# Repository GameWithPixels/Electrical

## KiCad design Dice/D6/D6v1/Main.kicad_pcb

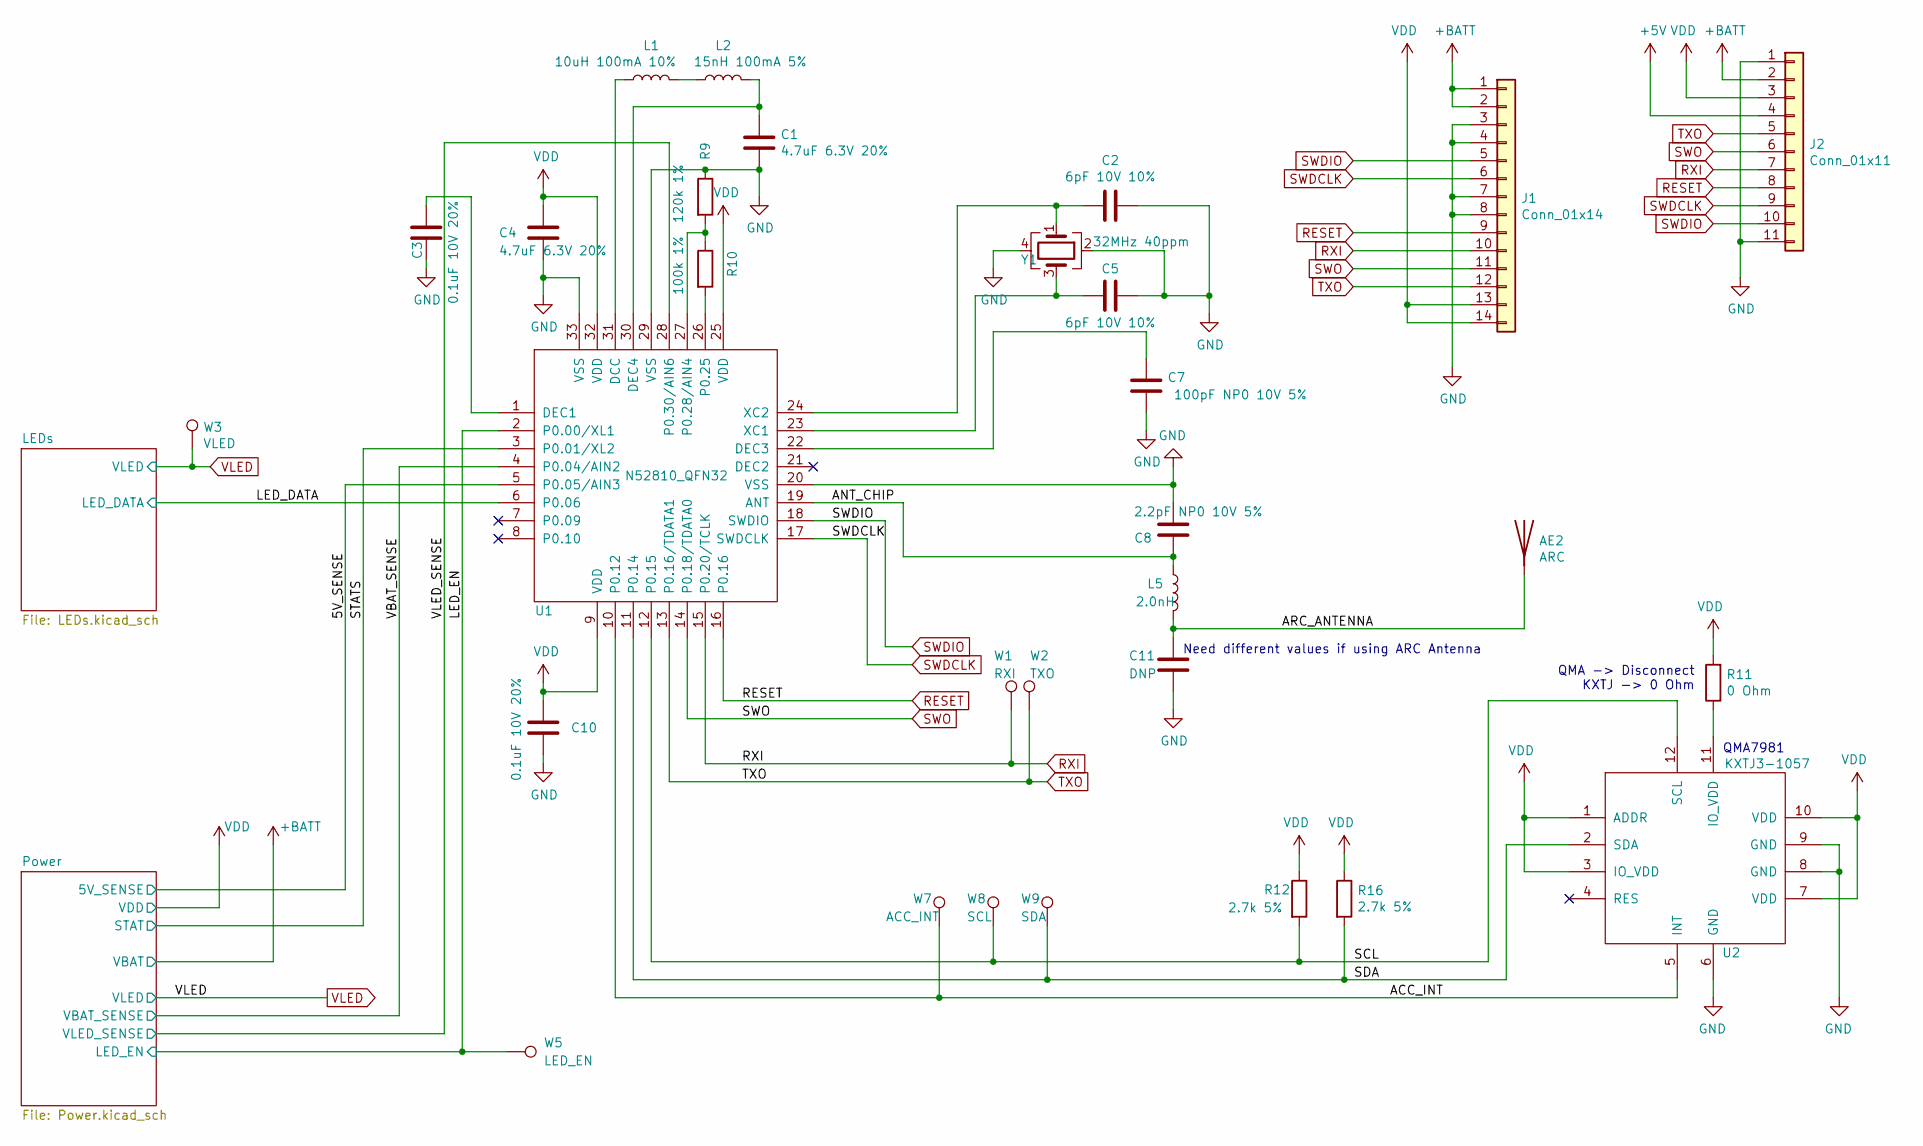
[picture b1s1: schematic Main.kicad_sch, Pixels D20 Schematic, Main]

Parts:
AE2: ARC; ARC_Antenna
C1, C4: 4.7uF 6.3V 20%; C_0402_1005Metric; Manufacturer Part Number GRM155R60J475ME87D
C2, C5: 6pF 10V 10%; C_0402_1005Metric; Manufacturer Part Number GCM1555C1H6R0DA16D
C3, C10: 0.1uF 10V 20%; C_0402_1005Metric; Manufacturer Part Number GRM155R61H104KE19D
C7: 100pF NP0 10V 5%; C_0402_1005Metric; Manufacturer Part Number C0402C101J5GAC7411
C8: 2.2pF NP0 10V 5%; C_0402_1005Metric
C11: DNP; C_0402_1005Metric
J1: Conn_01x14; FPC_14
J2: Conn_01x11; FPC-POGO-11
L1: 10uH 100mA 10%; L_0805_2012Metric; Manufacturer Part Number LBR2012T100K
L2: 15nH 100mA 5%; L_0402_1005Metric; Manufacturer Part Number HK100515NJ-T
L5: 2.0nH; L_0402_1005Metric
R9: 120k 1%; R_0402_1005Metric; Manufacturer Part Number CRCW0402100KFKEDC
R10: 100k 1%; R_0402_1005Metric; Manufacturer Part Number CRCW0402100KFKEDC
R11: 0 Ohm; R_0402_1005Metric; Manufacturer Part Number AC0402FR-070RL
R12, R16: 2.7k 5%; R_0402_1005Metric; Manufacturer Part Number RC0402JR-072K7L
U1: N52810_QFN32; QFN-32-1EP_5x5mm_P0.5mm_EP3.1x3.1mm; Manufacturer Part Number NRF52810-QCAA-R
U2: KXTJ3-1057; LGA-12_2x2mm_P0.5mm; Manufacturer Part Number KXTJ3-1057
W1: RXI; TEST_PIN
W2: TXO; TEST_PIN
W3: VLED; TEST_PIN
W5: LED_EN; TEST_PIN
W7: ACC_INT; TEST_PIN
W8: SCL; TEST_PIN
W9: SDA; TEST_PIN
Y1: 32MHz 40ppm; Crystal_SMD_2016-4Pin_2.0x1.6mm; Manufacturer Part Number XRCGB32M000F2P00R0

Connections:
+5V: J2.4; also elsewhere on the board
+BATT: J1.1, J1.2, J2.2; also elsewhere on the board
/5V_SENSE: U1.5 (P0.05/AIN3); also elsewhere on the board
/ACC_INT: U1.10 (P0.12), U2.5 (INT), W7.1
/ANT_CHIP: C8.1, L5.1, U1.19 (ANT)
/ARC_ANTENNA: AE2.1 (A), C11.1, L5.2
/LED_DATA: U1.6 (P0.06); also elsewhere on the board
/LED_EN: U1.2 (P0.00/XL1), W5.1; also elsewhere on the board
/SCL: R12.2, U1.12 (P0.15), U2.12 (SCL), W8.1
/SDA: R16.2, U1.11 (P0.14), U2.2 (SDA), W9.1
/STATS: U1.3 (P0.01/XL2); also elsewhere on the board
/VBAT_SENSE: U1.4 (P0.04/AIN2); also elsewhere on the board
/VLED_SENSE: U1.28 (P0.30/AIN6); also elsewhere on the board
GND: C1.2, C2.1, C3.2, C4.2, C5.1, C7.2, C8.2, C10.2, C11.2, J1.3, J1.4, J1.7, J1.8, J2.1, J2.11, R9.1, U1.20 (VSS), U1.29 (VSS), U1.33 (VSS), U2.6 (GND), U2.8 (GND), U2.9 (GND), Y1.2, Y1.4; also elsewhere on the board
unnamed: C1.1, L2.2, U1.30 (DEC4)
unnamed: C2.2, U1.24 (XC2), Y1.1
unnamed: C3.1, U1.1 (DEC1)
unnamed: C5.2, U1.23 (XC1), Y1.3
unnamed: C7.1, U1.22 (DEC3)
unnamed: L1.1, U1.31 (DCC)
unnamed: L1.2, L2.1
unnamed: R9.2, R10.1, U1.27 (P0.28/AIN4)
unnamed: R10.2, U1.26 (P0.25)
unnamed: R11.1, U2.11 (IO_VDD)
RESET: J1.9, J2.8, U1.16 (P0.16)
RXI: J1.10, J2.7, U1.15 (P0.20/TCLK), W1.1
SWDCLK: J1.6, J2.9, U1.17 (SWDCLK)
SWDIO: J1.5, J2.10, U1.18 (SWDIO)
SWO: J1.11, J2.6, U1.14 (P0.18/TDATA0)
TXO: J1.12, J2.5, U1.13 (P0.16/TDATA1), W2.1
VDD: C4.1, C10.1, J1.13, J1.14, J2.3, R11.2, R12.1, R16.1, U1.9 (VDD), U1.25 (VDD), U1.32 (VDD), U2.1 (ADDR), U2.3 (IO_VDD), U2.7 (VDD), U2.10 (VDD); also elsewhere on the board
VLED: W3.1; also elsewhere on the board

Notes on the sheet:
QMA -> Disconnect KXTJ -> 0 Ohm
Need different values if using ARC Antenna
QMA7981

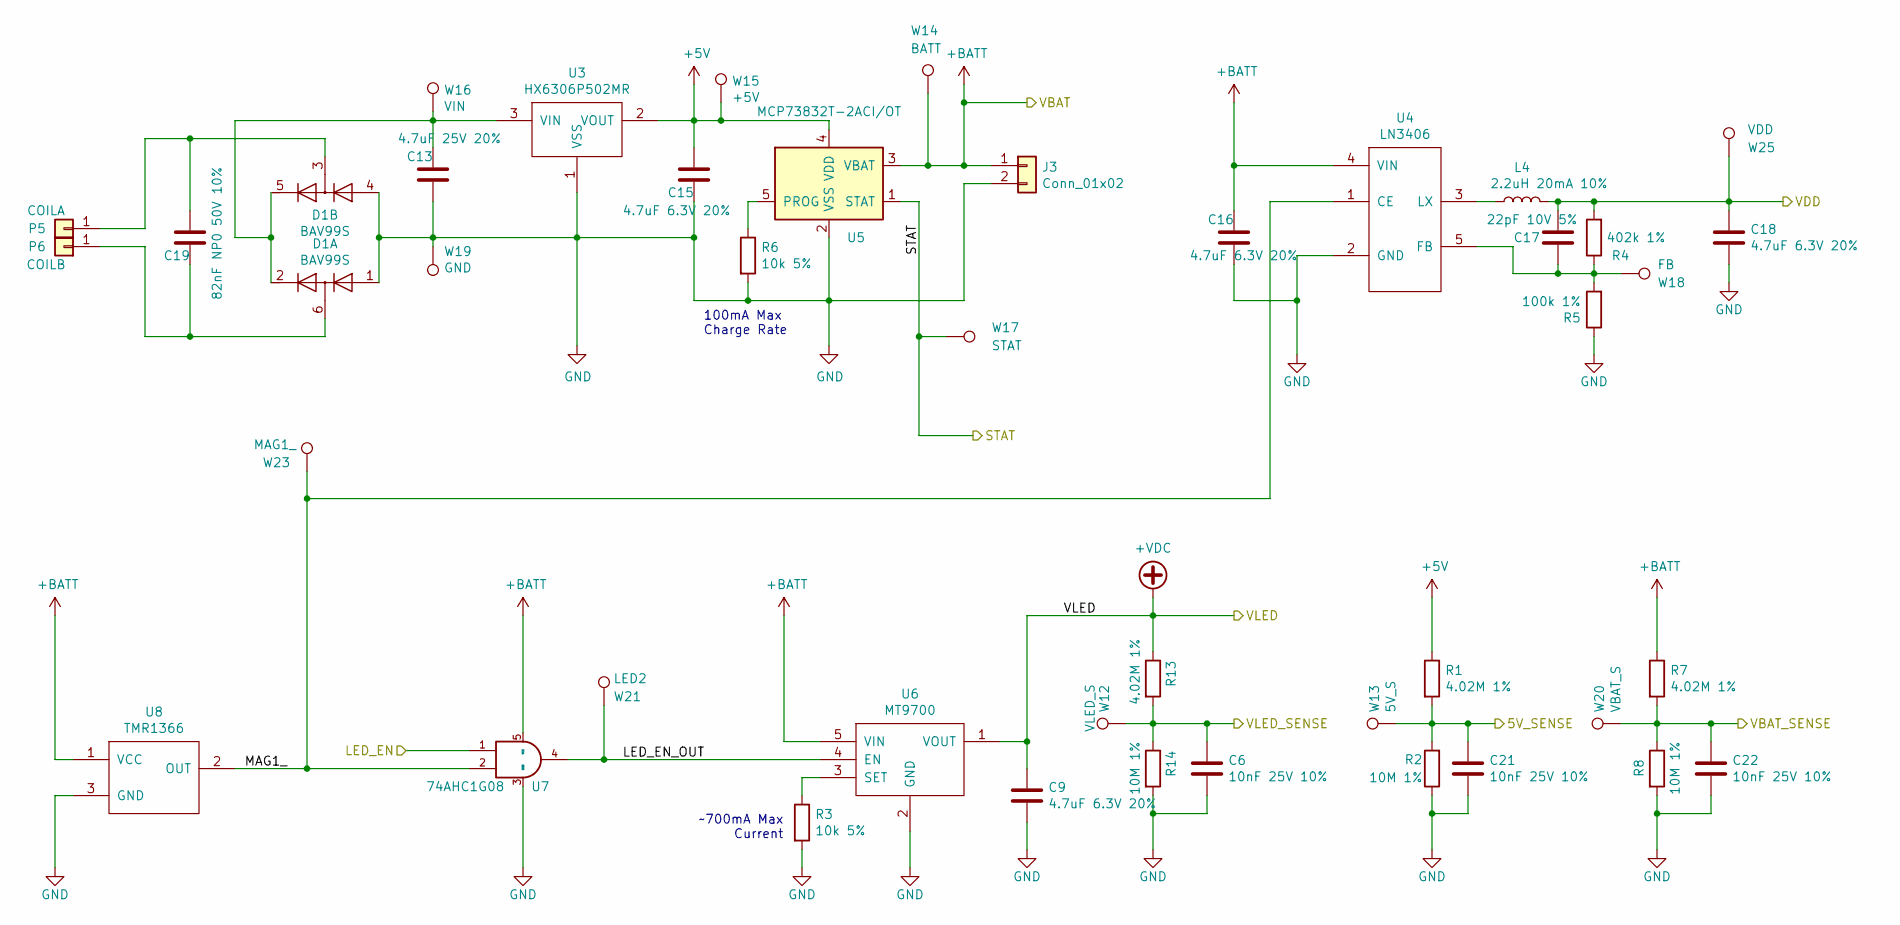
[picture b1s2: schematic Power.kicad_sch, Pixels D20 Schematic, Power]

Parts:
C6, C21, C22: 10nF 25V 10%; C_0402_1005Metric; Manufacturer Part Number AC0402KPX7R9BB103
C9, C15, C16, C18: 4.7uF 6.3V 20%; C_0402_1005Metric; Manufacturer Part Number GRM155R60J475ME87D
C13: 4.7uF 25V 20%; C_0603_1608Metric; Manufacturer Part Number GRM188R61E475KE11D
C17: 22pF 10V 5%; C_0402_1005Metric; Manufacturer Part Number CC0402JRNPO9BN220
C19: 82nF NP0 50V 10%; C_0805_2012Metric
D1: BAV99S; SOT-363_SC-70-6; Manufacturer Part Number BAV99SH6327XTSA1
J3: Conn_01x02; Hongjie 10100 Connector
L4: 2.2uH 20mA 10%; L_0805_2012Metric; Manufacturer Part Number CV201210-2R2K
P5: COILA; TestPoint_THTPad_D1.5mm_Drill0.7mm
P6: COILB; TestPoint_THTPad_D1.5mm_Drill0.7mm
R1, R7, R13: 4.02M 1%; R_0402_1005Metric; Manufacturer Part Number CRCW04024M02FKED
R2, R8, R14: 10M 1%; R_0402_1005Metric; Manufacturer Part Number RC0402FR-0710ML
R3, R6: 10k 5%; R_0402_1005Metric; Manufacturer Part Number RC0402JR-0710KL
R4: 402k 1%; R_0402_1005Metric; Manufacturer Part Number RC0402FR-07402KL
R5: 100k 1%; R_0402_1005Metric; Manufacturer Part Number CRCW0402100KFKEDC
U3: HX6306P502MR; SOT-23; Manufacturer Part Number HX6306P502MR
U4: LN3406; SOT-23-5; Manufacturer Part Number XT3406AFMR-G
U5: MCP73832T-2ACI/OT; SOT-23-5; Manufacturer Part Number MCP73832T-2ACI/OT
U6: MT9700; SOT-23-5; Manufacturer Part Number MT9700
U7: 74AHC1G08; SOT-353_SC-70-5; Manufacturer Part Number SN74AHC1G08DCKR
U8: TMR1366; SOT-23; Manufacturer Part Number TMR1366S
W12: VLED_S; TEST_PIN
W13: 5V_S; TEST_PIN
W14: BATT; TEST_PIN
W15: +5V; TEST_PIN
W16: VIN; TEST_PIN
W17: STAT; TEST_PIN
W18: FB; TEST_PIN
W19: GND; TEST_PIN
W20: VBAT_S; TEST_PIN
W21: LED2; TEST_PIN
W23: MAG1_; TEST_PIN
W25: VDD; TEST_PIN

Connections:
+5V: C15.1, R1.1, U3.2 (VOUT), U5.4 (VDD), W15.1; also elsewhere on the board
+BATT: C16.1, J3.1, R7.1, U4.4 (VIN), U5.3 (VBAT), U6.5 (VIN), U7.5 (VCC), U8.1 (VCC), W14.1; also elsewhere on the board
/5V_SENSE: C21.1, R1.2, R2.2, W13.1; also elsewhere on the board
/LED_EN: U7.1; also elsewhere on the board
/Power/LED_EN_OUT: U6.4 (EN), U7.4, W21.1
/Power/MAG1_: U4.1 (CE), U7.2, U8.2 (OUT), W23.1
/STATS: U5.1 (STAT), W17.1; also elsewhere on the board
/VBAT_SENSE: C22.1, R7.2, R8.1, W20.1; also elsewhere on the board
/VLED_SENSE: C6.1, R13.2, R14.1, W12.1; also elsewhere on the board
GND: C6.2, C9.2, C13.2, C15.2, C16.2, C18.2, C21.2, C22.2, D1.1 (A1), D1.4 (A3), J3.2, R2.1, R3.2, R5.1, R6.2, R8.2, R14.2, U3.1 (VSS), U4.2 (GND), U5.2 (VSS), U6.2 (GND), U7.3 (GND), U8.3 (GND), W19.1; also elsewhere on the board
unnamed: C13.1, D1.2 (K2), D1.5 (K4), U3.3 (VIN), W16.1
unnamed: C17.2, R4.1, R5.2, U4.5 (FB), W18.1
unnamed: C19.1, D1.3 (K1A2), P5.1
unnamed: C19.2, D1.6 (K3A4), P6.1
unnamed: L4.1, U4.3 (LX)
unnamed: R3.1, U6.3 (SET)
unnamed: R6.1, U5.5 (PROG)
VDD: C17.1, C18.1, L4.2, R4.2, W25.1; also elsewhere on the board
VLED: C9.1, R13.1, U6.1 (VOUT); also elsewhere on the board

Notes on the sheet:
~700mA Max Current
100mA Max Charge Rate

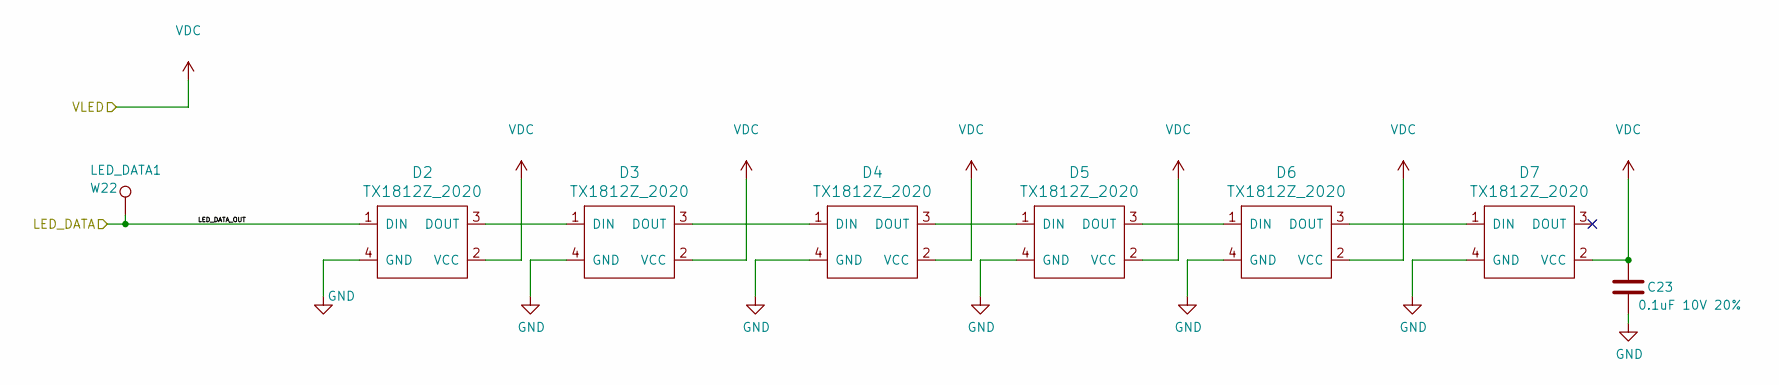
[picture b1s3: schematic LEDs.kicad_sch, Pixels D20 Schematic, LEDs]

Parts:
C23: 0.1uF 10V 20%; C_0402_1005Metric; Manufacturer Part Number GRM155R61H104KE19D
D2, D3, D4, D5, D6, D7: TX1812Z_2020; Manufacturer Part Number TX1812Z 2020
W22: LED_DATA1; TEST_PIN

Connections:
/LED_DATA: D2.1 (DIN), W22.1; also elsewhere on the board
GND: C23.2, D2.4 (GND), D3.4 (GND), D4.4 (GND), D5.4 (GND), D6.4 (GND), D7.4 (GND); also elsewhere on the board
unnamed: D2.3 (DOUT), D3.1 (DIN)
unnamed: D3.3 (DOUT), D4.1 (DIN)
unnamed: D4.3 (DOUT), D5.1 (DIN)
unnamed: D5.3 (DOUT), D6.1 (DIN)
unnamed: D6.3 (DOUT), D7.1 (DIN)
VLED: C23.1, D2.2 (VCC), D3.2 (VCC), D4.2 (VCC), D5.2 (VCC), D6.2 (VCC), D7.2 (VCC); also elsewhere on the board

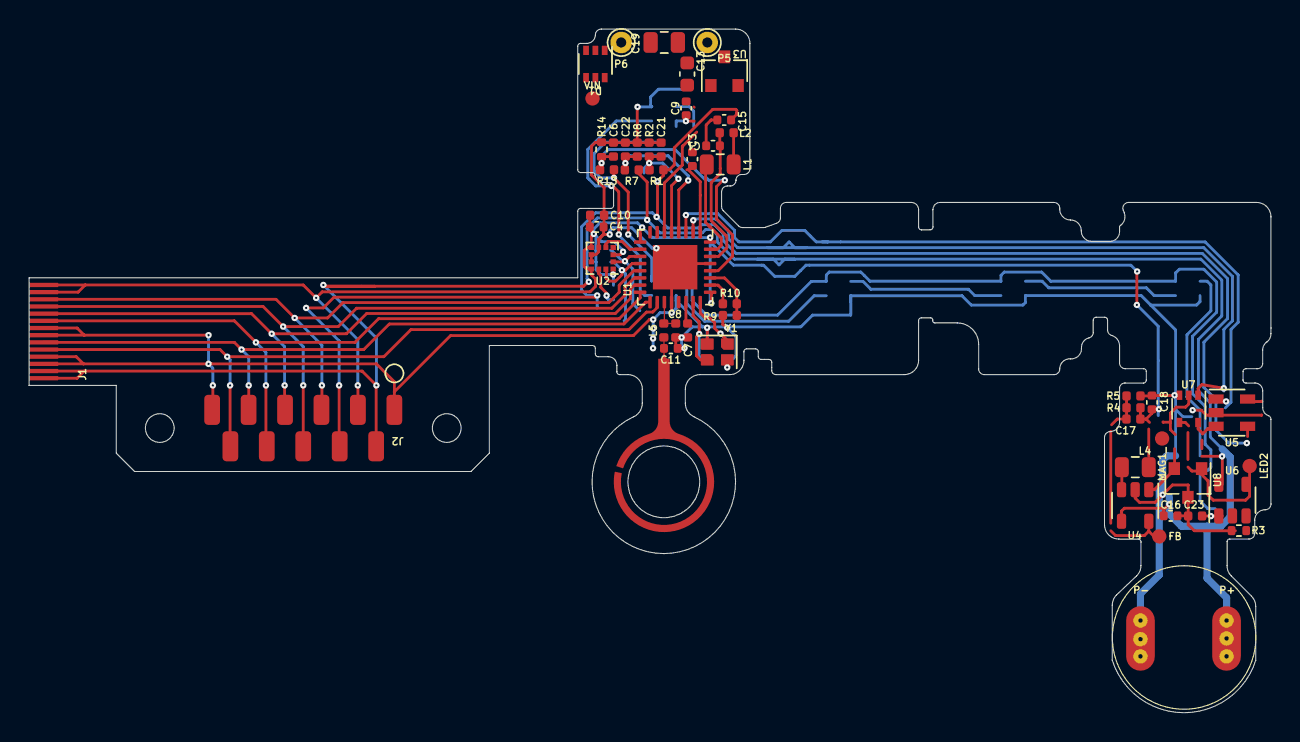
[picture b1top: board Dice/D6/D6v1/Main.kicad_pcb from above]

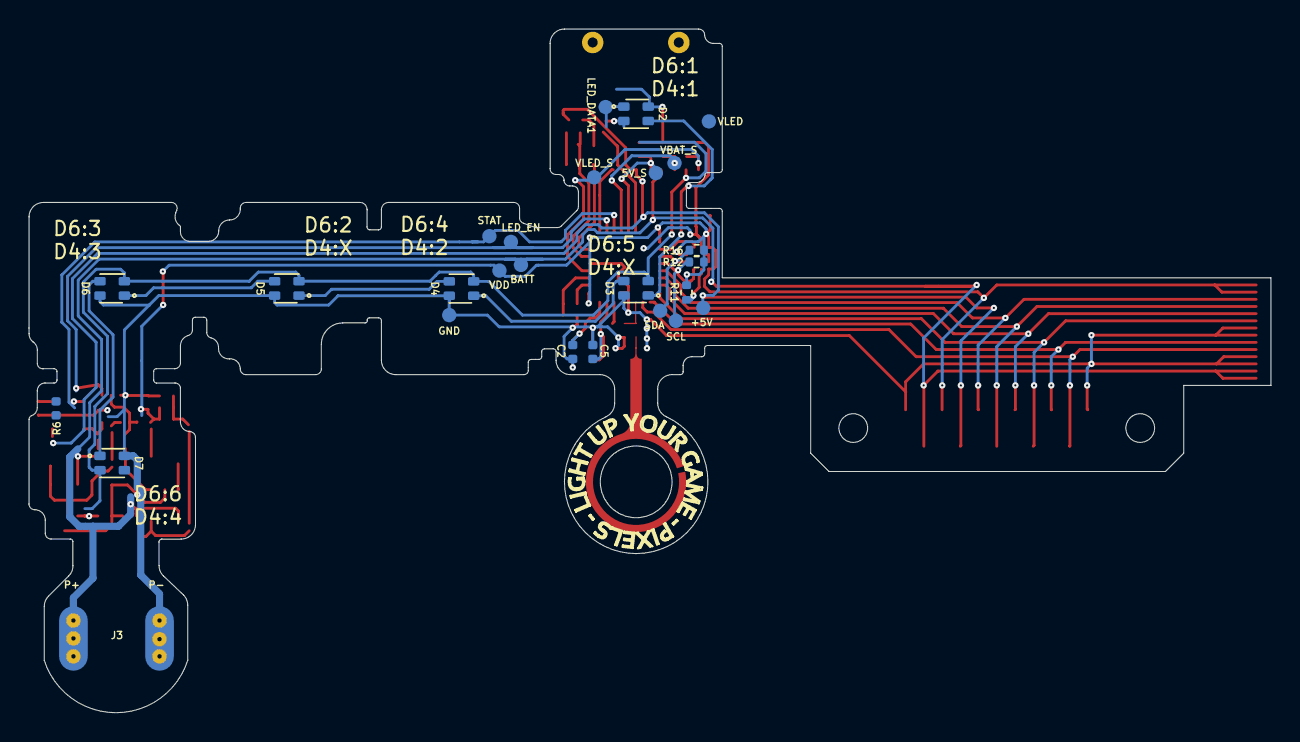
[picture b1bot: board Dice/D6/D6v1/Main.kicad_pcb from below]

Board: 2 copper layers, 86.6 x 47.6 mm, 78 parts (26 on the bottom side), 46 nets.

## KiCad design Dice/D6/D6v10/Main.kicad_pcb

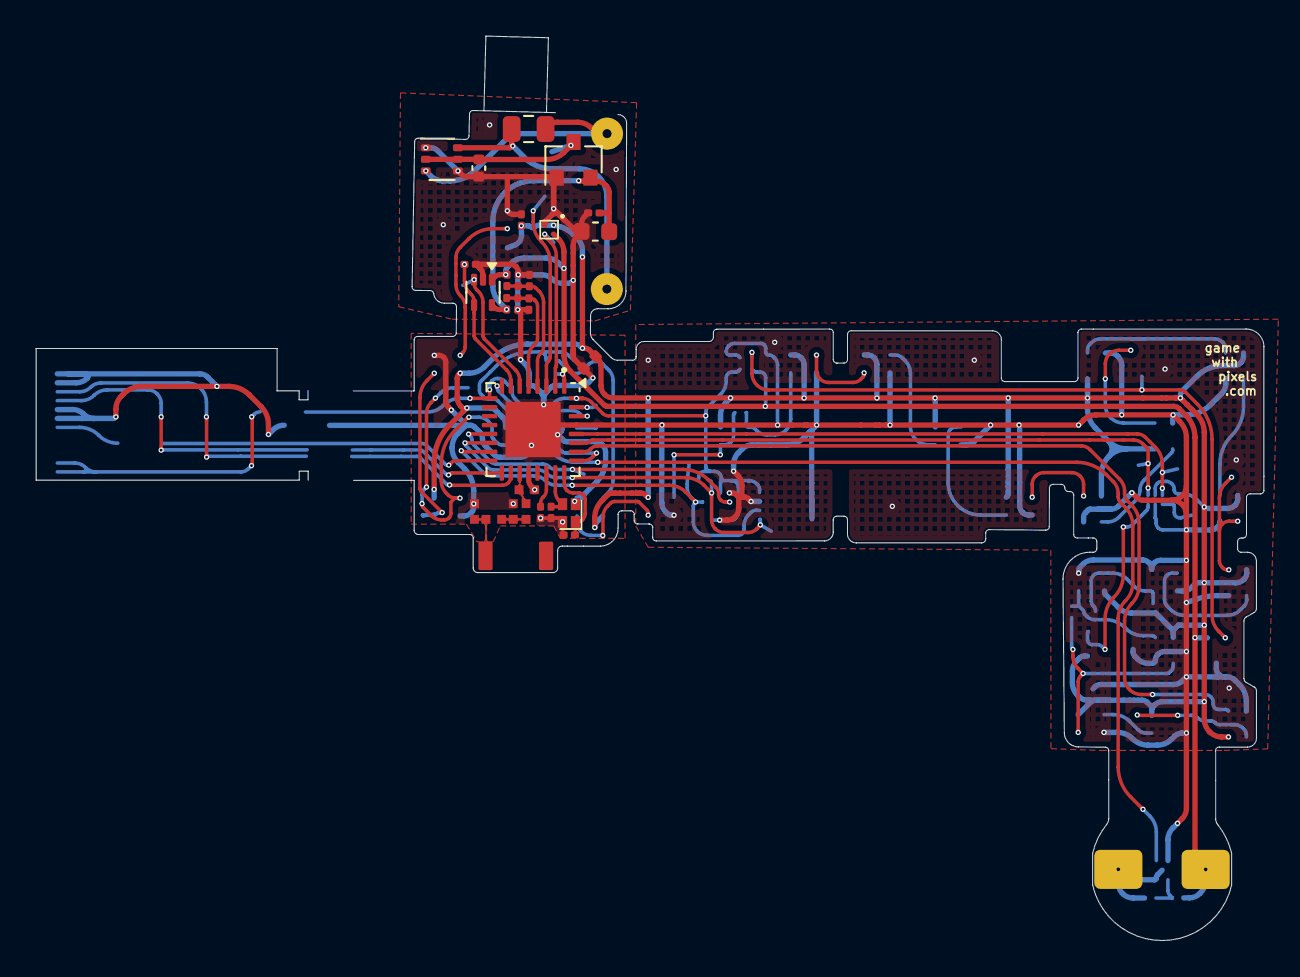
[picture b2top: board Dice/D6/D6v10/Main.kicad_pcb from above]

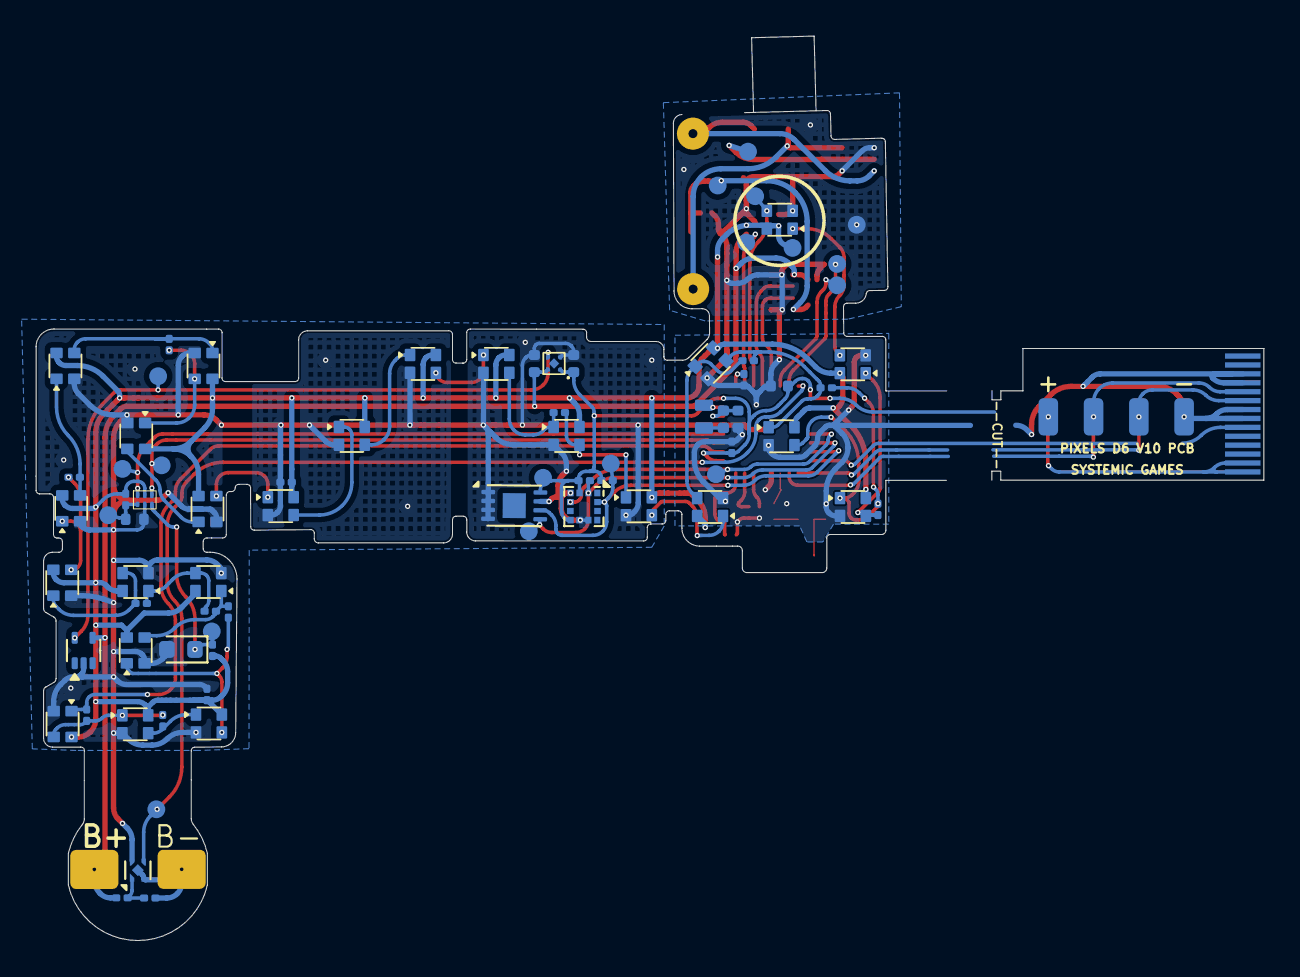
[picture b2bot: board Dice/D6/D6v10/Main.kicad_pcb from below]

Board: 2 copper layers, 68.9 x 50.7 mm, 110 parts (82 on the bottom side), 62 nets.

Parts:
AE1: Antenna_Chip; CHIP_ANT
C1, C4, C18: 4.7uF 10V 20%; C_0402_1005Metric
C2, C5: 8pF 10V 10%; C_0201_0603Metric
C3, C6, C10, C23, C24, C25: 0.1uF 10V 20%; C_0201_0603Metric
C7: 100pF NP0 10V 2%; C_0201_0603Metric
C8: 0.8pF 10V 5% C0G; 0402_RF
C9, C16: 10uF 6.3V 20%; C_0402_1005Metric
C11, C12: DNP; 0402_RF
C13: 4.7uF 25V 20%; C_0402_1005Metric
C15: 22uF 10V 20%; C_0603_1608Metric
C19: 12nF 50V 5% NP0; C_0805_2012Metric
C21, C22: 10nF 25V 10%; C_0201_0603Metric
D1: BAV99S; SOT-363_SC-70-6
D2, D3, D4, D5, D6, D7, D8, D9, D11, D12, D13, D15, D16, D17, D18, D19, D20, D21, D22, D23, D24, D25, D26, D27: TX1812MJA5; TX1812MWCA5-F01
J1: Conn_01x14; FPC_14
J2: Conn_01x04; FPC-POGO-4
J3: Conn_01x02; Hongjie 10100 Solder Tabs
L1: 10uH 100mA 20%; C_1.2x1.8
L2: 15nH 100mA 5%; L_0402_1005Metric
L3: 0 Ohm; 0402_RF
L5: 3.9nH 5%; 0402_RF
P5: COILA; TestPoint_THTPad_D1.5mm_Drill0.7mm_nosilk
P6: COILB; TestPoint_THTPad_D1.5mm_Drill0.7mm_nosilk
Q1: ZSPT-Z1608C-06F-Z4; D_0603_1608Metric
R1, R2, R7: 3.9M 1%; R_0201_0603Metric
R3, R13, R14, R15, R16, R17, R18, R19, R20, R21, R22: 0R; R_0201_0603Metric
R4, R5: 10k 1%; R_0201_0603Metric
R6, R10, R11: 3.9k 1%; R_0201_0603Metric
R8: 10M 1%; R_0201_0603Metric
R9: 100k 1%; R_0201_0603Metric
R12: 510R 1%; R_0201_0603Metric
TH1: NTC 100k @ 25C; R_0402_1005Metric
U1: N52810_QFN32; QFN-32-1EP_5x5mm_P0.5mm_EP3.1x3.1mm
U2: SC7A20HTR; LGA-12_2x2mm_P0.5mm
U3: PJ75BL50SA; SOT-23
U4: ME6230; FPB1_1-4
U5: BL24C02F-NTRC; TDFN-8-1EP_3x2mm_P0.5mm_EP1.3x1.4mm
U6: AW35122
U7: DS6101; UDFN-4-1EP_1x1mm_P0.65mm_EP0.48x0.48mm
U8: SL1605; SOT-553
U9: XT4051; SOT-553
U10: WAS3157D-6/TR; DFN1109-6
W1: LED_DATA1; TEST_PIN
W2: PROG; TEST_PIN
W3: PHOTO; TEST_PIN
W4: VDC; TEST_PIN
W5: SM; TEST_PIN
W6: MAG1; TEST_PIN
W7: ACC_INT; TEST_PIN
W8: SCL; TEST_PIN
W9: SDA; TEST_PIN
W15: +5V; TEST_PIN
W16: VIN; TEST_PIN
W17: STAT; TEST_PIN
W19: GND; TEST_PIN
W20: TH1; TEST_PIN
W21: LED2; TEST_PIN
W22: ADC_SELECT; TEST_PIN
W23: ADC_OUT; TEST_PIN
W25: VDD; TEST_PIN
Y1: 32MHz 40ppm; SX16Y032000B81T001

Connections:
+5V: C15.1, R1.1, R4.1, U3.2 (VOUT), U9.5 (VCC), W15.1
+BATT: C16.1, J3.1, R7.1, R12.1, U4.4 (VIN), U6.A2 (VIN), U8.4 (VDD), U9.1 (BAT)
/5V_SENSE: C21.1, R1.2, R2.2, U1.5 (P0.05/AIN3)
/ACC_INT: U1.13 (P0.16/TDATA1), U2.5 (INT1), W7.1
/ANTENNA: AE1.1 (FEED), C11.1, L3.2
/ANT_50: C12.1, L3.1, L5.2
/ANT_NRF: C8.1, L5.1, U1.19 (ANT)
/LED_DATA: D2.3 (DIN), U1.3 (P0.01/XL2), W1.1
/LED_EN: U1.2 (P0.00/XL1), U6.B2 (EN), W21.1
/LED_RETURN: D27.1 (DOUT), R22.2, U1.26 (P0.25)
/MAG1_: U4.3 (CE), U8.5 (OUT), W6.1
/NTC_PHOTO_SENSE: U1.28 (P0.30/AIN6), U10.6 (A), W23.1
/OPT_A2D: Q1.1 (C), R5.2, U10.3 (B1), W3.1
/PROG: R6.1, U1.7 (P0.09), U9.4 (PROG), W2.1
/SCL: R10.2, U1.15 (P0.20/TCLK), U2.12 (SCL), U5.6 (SCL), W8.1
/SDA: R11.2, U1.14 (P0.18/TDATA0), U2.2 (SDA), U5.5 (SDA), W9.1
/SENSE_SELECT: U1.27 (P0.28/AIN4), U10.4 (S), W22.1
/SM: U1.8 (P0.10), U7.3 (SM), W5.1
/STATS: U1.6 (P0.06), U9.3 (CHRG), W17.1
/VBAT_SENSE: C22.1, R7.2, R8.1, U1.4 (P0.04/AIN2)
/Wireless Charging/B-: C23.2, J3.2, U7.2 (VSS), U7.5 (PAD)
/Wireless Charging/COILA: C19.1, D1.3 (K1A2), P5.1
/Wireless Charging/COILB: C19.2, D1.6 (K3A4), P6.1
/Wireless Charging/TH1: R9.2, TH1.1, U10.1 (B0), W20.1
GND: C1.2, C2.1, C3.2, C4.2, C5.1, C6.2, C7.2, C8.2, C9.2, C10.2, C11.2, C12.2, C13.2, C15.2, C16.2, C18.2, C21.2, C22.2, C24.2, C25.2, D1.1 (A1), D1.4 (A3), D2.2 (GND), D3.2 (GND), D4.2 (GND), D5.2 (GND), D6.2 (GND), D7.2 (GND), D8.2 (GND), D9.2 (GND), D11.2 (GND), D12.2 (GND), D13.2 (GND), D15.2 (GND), D16.2 (GND), D17.2 (GND), D18.2 (GND), D19.2 (GND), D20.2 (GND), D21.2 (GND), D22.2 (GND), D23.2 (GND), D24.2 (GND), D25.2 (GND), D26.2 (GND), D27.2 (GND), J1.3, J1.4, J1.7, J1.8, J2.4, Q1.2 (E), R2.1, R4.2, R6.2, R8.2, TH1.2, U1.20 (VSS), U1.29 (VSS), U1.33 (VSS), U2.4 (NC), U2.8 (GND), U2.9 (GND), U3.1 (VSS), U4.2 (VSS), U5.1 (A0), U5.2 (A1), U5.3 (A2), U5.4 (GND), U5.7 (WP), U6.B1 (GND), U7.4 (EB-), U8.2 (GND), U9.2 (GND), U10.2 (GND), W19.1, Y1.2, Y1.4
unnamed: D2.1 (DOUT), D3.3 (DIN)
unnamed: D3.1 (DOUT), D4.3 (DIN), R14.1
unnamed: D4.1 (DOUT), D5.3 (DIN), R3.1, R14.2
unnamed: D5.1 (DOUT), D6.3 (DIN), R3.2, R15.1
unnamed: D6.1 (DOUT), D7.3 (DIN), R15.2
unnamed: D7.1 (DOUT), D8.3 (DIN)
unnamed: D8.1 (DOUT), D9.3 (DIN), R13.1
unnamed: D9.1 (DOUT), D11.3 (DIN), R13.2
unnamed: D11.1 (DOUT), D12.3 (DIN)
unnamed: D12.1 (DOUT), D13.3 (DIN)
unnamed: D13.1 (DOUT), D15.3 (DIN)
unnamed: D15.1 (DOUT), D16.3 (DIN)
unnamed: D16.1 (DOUT), D17.3 (DIN)
unnamed: D17.1 (DOUT), D18.3 (DIN), R16.1
unnamed: D18.1 (DOUT), D19.3 (DIN), R16.2
unnamed: D19.1 (DOUT), D20.3 (DIN), R17.1
unnamed: D20.1 (DOUT), D21.3 (DIN), R17.2
unnamed: D21.1 (DOUT), D22.3 (DIN), R19.1
unnamed: D22.1 (DOUT), D23.3 (DIN), R19.2, R20.1
unnamed: D23.1 (DOUT), D24.3 (DIN), R18.1, R20.2
unnamed: D24.1 (DOUT), D25.3 (DIN), R18.2
unnamed: D25.1 (DOUT), D26.3 (DIN), R21.1
unnamed: D26.1 (DOUT), D27.3 (DIN), R21.2, R22.1
unnamed: L1.2, L2.1
unnamed: L1.1, U1.31 (DCC)
unnamed: C3.1, U1.1 (DEC1)
unnamed: C7.1, U1.22 (DEC3)
unnamed: C1.1, L2.2, U1.30 (DEC4)
unnamed: C5.2, U1.23 (XC1), Y1.3
unnamed: C2.2, U1.24 (XC2), Y1.1
unnamed: C23.1, R12.2, U7.1 (BAT)
RESET: J1.9, U1.16 (P0.16)
SWDCLK: J1.6, J2.3, U1.17 (SWDCLK)
SWDIO: J1.5, J2.2, U1.18 (SWDIO)
VDC: C6.1, C9.1, C24.1, C25.1, D2.4 (VCC), D3.4 (VCC), D4.4 (VCC), D5.4 (VCC), D6.4 (VCC), D7.4 (VCC), D8.4 (VCC), D9.4 (VCC), D11.4 (VCC), D12.4 (VCC), D13.4 (VCC), D15.4 (VCC), D16.4 (VCC), D17.4 (VCC), D18.4 (VCC), D19.4 (VCC), D20.4 (VCC), D21.4 (VCC), D22.4 (VCC), D23.4 (VCC), D24.4 (VCC), D25.4 (VCC), D26.4 (VCC), D27.4 (VCC), R5.1, R9.1, U6.A1 (VOUT), U10.5 (VCC), W4.1
VDD: C4.1, C10.1, C18.1, J1.13, J1.14, J2.1, R10.1, R11.1, U1.9 (VDD), U1.25 (VDD), U1.32 (VDD), U2.3 (IO_VDD), U2.7 (VDD), U4.1 (VOUT), U5.8 (VCC), W25.1
VEE: C13.1, D1.2 (K2), D1.5 (K4), U3.3 (VIN), W16.1

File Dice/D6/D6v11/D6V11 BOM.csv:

"Reference","Qty","Value","DNP","Footprint","Manufacturer","Part Number"
"AE1","1","Antenna_Chip","","Pixels-dice:CHIP_ANT","Microgate","MGMA3216H2450-A02"
"C1,C4,C18","3","4.7uF 10V 20%","","Pixels-dice:C_0402_1005Metric","HRE","CGA0402X5R475M100GT"
"C2,C5","2","8pF 10V 10%","","Capacitor_SMD:C_0201_0603Metric","HRE","CGA0201C0G8R0B250ET"
"C3,C6,C10,C23,C24,C25","6","0.1uF 10V 20%","","Capacitor_SMD:C_0201_0603Metric","HRE","CGA0201X5R104K100ET"
"C7","1","100pF NP0 10V 2%","","Capacitor_SMD:C_0201_0603Metric","HRE","CGA0201C0G101J500ET"
"C8","1","0.8pF 10V 5% C0G","","Capacitor_SMD:C_0201_0603Metric","HRE","CGA0201C0GR80C250ET"
"C9,C16","2","10uF 6.3V 20%","","Pixels-dice:C_0402_1005Metric","HRE","CGA0402X5R106M6R3GT"
"C13","1","4.7uF 25V 20%","","Capacitor_SMD:C_0402_1005Metric","HRE","CGA0402X5R475M250GT"
"C15","1","22uF 10V 20%","","Capacitor_SMD:C_0603_1608Metric","HRE","CGA0603X5R226M100JT"
"C19","1","12nF 50V 5% NP0","","Capacitor_SMD:C_0805_2012Metric","Murata","GRM2195C1H123JA01D"
"C21,C22","2","10nF 25V 10%","","Capacitor_SMD:C_0201_0603Metric","HRE","CGA0201X5R103K250ET"
"D1","1","BAV99S","","Pixels-dice:SOT-363_SC-70-6","Nexperia","BAV99S,115"
"D2,D3,D4,D5,D6,D7,D8,D9,D11,D12,D13,D15,D16,D17,D18,D19,D20,D21,D22,D23,D24,D25,D26,D27","24","TX1812MJA5","","Pixels-dice:TX1812MWCA5-F01","TCWIN","TX1812MJA5-F01"
"L1","1","10uH 100mA 20%","","Inductor_SMD:L_0603_1608Metric","FH","CMI160808J100KT"
"L2","1","15nH 100mA 5%","","Inductor_SMD:L_0201_0603Metric","FH","VHF060303HQ15NKT"
"L3","1","0 Ohm","","Resistor_SMD:R_0201_0603Metric","UNI-ROYAL(Uniroyal Elec)","0201WMF0000TEE"
"L5","1","3.9nH 5%","","Inductor_SMD:L_0201_0603Metric","FH"," VHF060303HQ3N9ST02"
"R1,R2,R7","3","3.9M 1%","","Resistor_SMD:R_0201_0603Metric","UNI-ROYAL(Uniroyal Elec)","0201WMF3904TEE"
"R3","1","41.2k 1%","","Resistor_SMD:R_0201_0603Metric","UNI-ROYAL(Uniroyal Elec)","0201WMF4122TEE"
"R4","1","10k 1%","","Resistor_SMD:R_0201_0603Metric","UNI-ROYAL(Uniroyal Elec)","0201WMF1002TEE"
"R5,R9","2","100k 1%","","Resistor_SMD:R_0201_0603Metric","UNI-ROYAL(Uniroyal Elec)","0201WMF1003TEE"
"R6","1","3.57k 1%","","Resistor_SMD:R_0201_0603Metric","UNI-ROYAL(Uniroyal Elec)","0201WMF3571TEE"
"R8","1","10M 1%","","Resistor_SMD:R_0201_0603Metric","UNI-ROYAL(Uniroyal Elec)","0201WMF1005TEE"
"R10,R11","2","3.9k 1%","","Resistor_SMD:R_0201_0603Metric","UNI-ROYAL(Uniroyal Elec)","0201WMF3651TEE"
"R12","1","510R 1%","","Resistor_SMD:R_0201_0603Metric","UNI-ROYAL(Uniroyal Elec)","NQ01WMJ0511TEE"
"TH1","1","NTC 100k @ 25C","","Resistor_SMD:R_0201_0603Metric","muRata ","NCP03WF104F05RL "
"U1","1","N52810_QFN32","","Pixels-dice:QFN-32-1EP_5x5mm_P0.5mm_EP3.1x3.1mm","Nordic Semiconductor","NRF52810-QCAA-R"
"U2","1","SC7A20HTR","","Package_LGA:LGA-12_2x2mm_P0.5mm","Hangzhou Silan Microelectronics","SC7A20HTR"
"U3","1","PJ75BL50SA","","Pixels-dice:SOT-23","PJSEMI","PJ75BL50SA"
"U4","1","ME6230","","Pixels-dice:FPB1_1-4","MICRONE(Nanjing Micro One Elec)","ME6230C30U4AG"
"U5","1","BL24C02F-NTRC","","Pixels-dice:TDFN-8-1EP_3x2mm_P0.5mm_EP1.3x1.4mm","BL","BL24C02F-NTRC"
"U6","1","AW35122","","Pixels-dice:AW35122","AWINIC(Shanghai Awinic Tech)","AW35122FDR"
"U7","1","DS6101","","Package_DFN_QFN:UDFN-4-1EP_1x1mm_P0.65mm_EP0.48x0.48mm","DSTECH"," DS6101AED4"
"U8","1","SL1605","","Package_TO_SOT_SMD:SOT-553","Slkor(SLKORMICRO Elec.)","SL1605TL"
"U9","1","XT4051","","Package_TO_SOT_SMD:SOT-553","NATLINEAR","XT4051K421KR-G"
"Y1","1","32MHz 40ppm","","Pixels-dice:Crystal_SMD_2016-4Pin_2.0x1.6mm","TOGNJING","XTM20032000DT00351001"
